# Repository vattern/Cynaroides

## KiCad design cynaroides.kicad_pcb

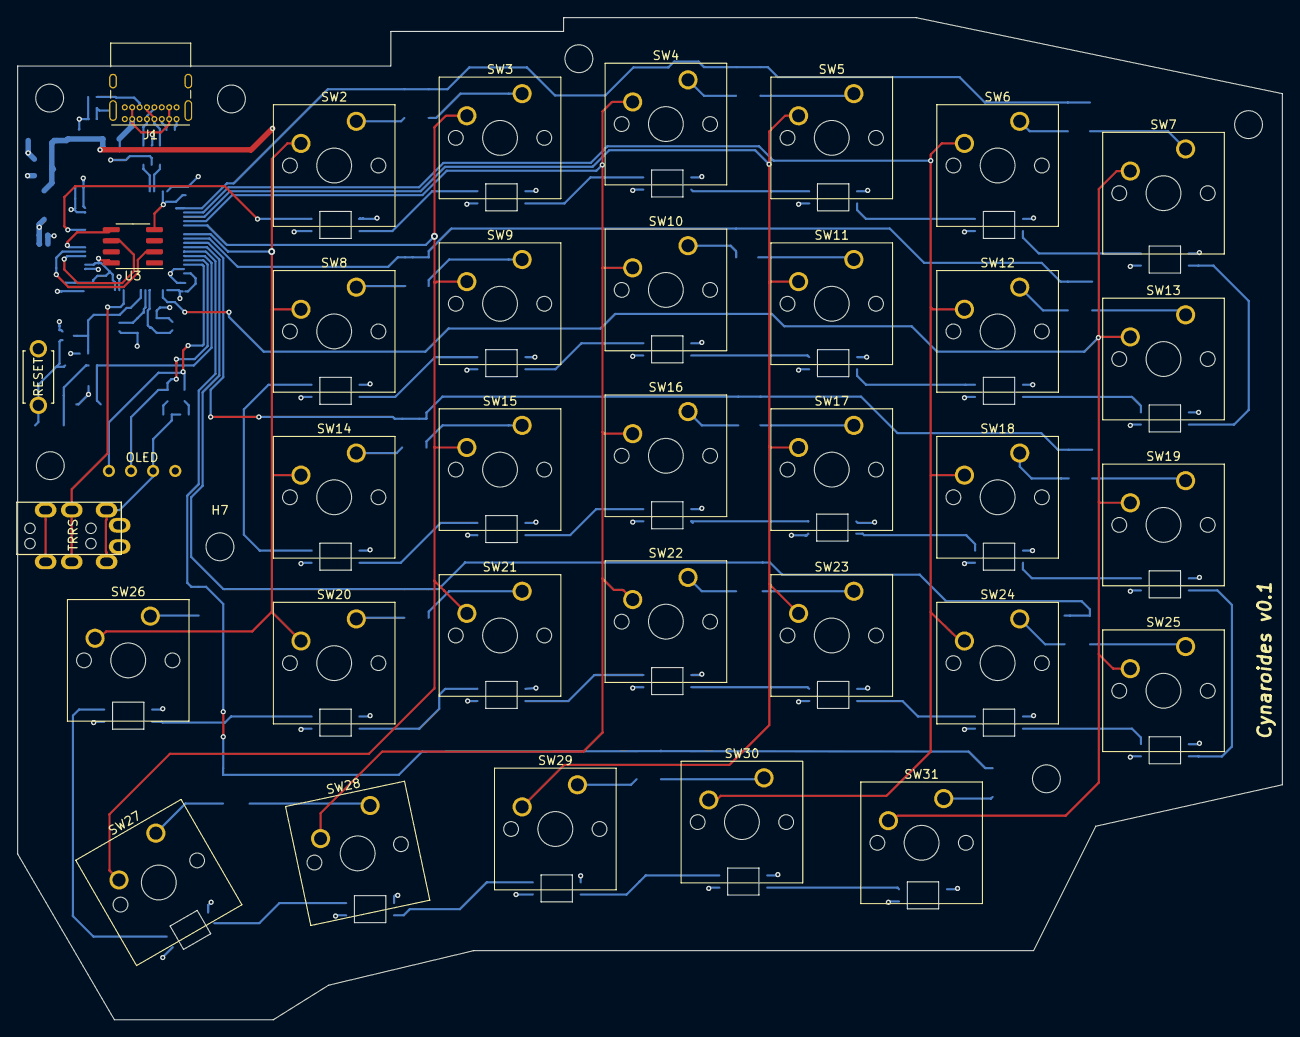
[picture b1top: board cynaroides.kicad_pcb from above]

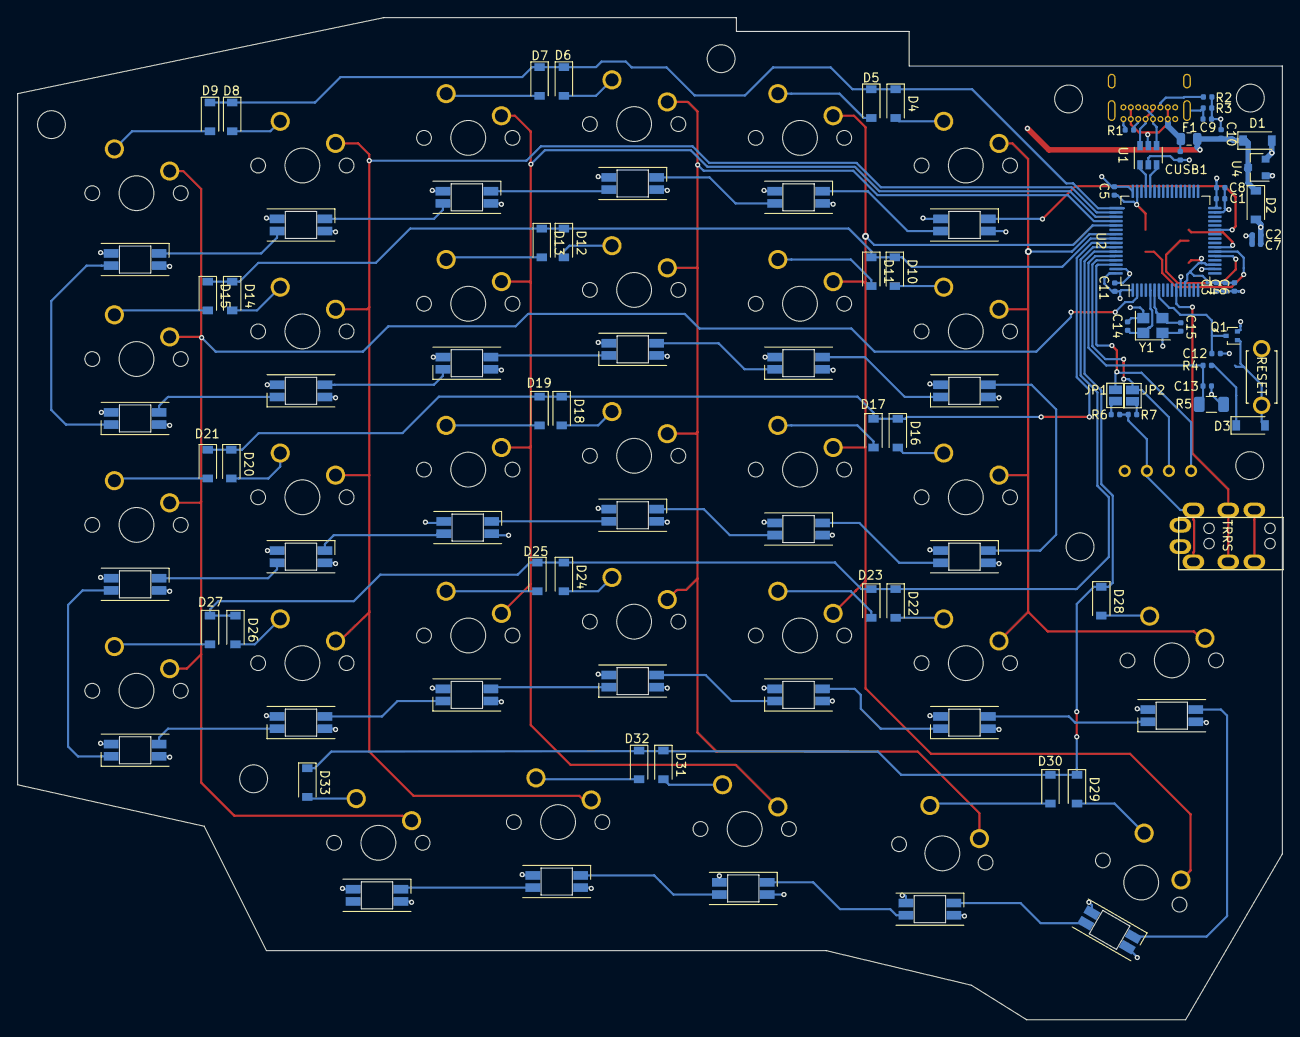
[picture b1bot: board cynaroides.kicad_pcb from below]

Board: 4 copper layers, 145.2 x 115.0 mm, 136 parts (94 on the bottom side), 96 nets.

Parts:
C1, C2, C5, C6, C10, C11, C12: 100n; C_0402_1005Metric
C3: 10n; C_0402_1005Metric
C4: 1u; C_0402_1005Metric
C7, C8: 4u7; C_0402_1005Metric
C9: 4n7; C_0402_1005Metric
C13: 100u; C_0402_1005Metric
C14, C15: 22p; C_0402_1005Metric
CUSB1: 100n; C_0402_1005Metric
D1: D_Schottky; D_SOD-123
D2: D_TVS; D_SOD-123
D3, D4, D5, D6, D7, D8, D9, D10, D11, D12, D13, D14, D15, D16, D17, D18, D19, D20, D21, D22, D23, D24, D25, D26, D27, D28, D29, D30, D31, D32, D33: 1N4148W; D_SOD-123
D34, D35, D36, D37, D38, D39, D40, D41, D42, D43, D44, D45, D46, D47, D48, D49, D50, D51, D52, D53, D54, D55, D56, D57, D58, D59, D60, D61, D62, D63: SK6812MINI; YS-SK6812MINI-E
F1: Polyfuse_Small; Fuse_0805_2012Metric
H1, H2, H3, H4, H5, H6, H7: MountingHole; MountingHole_3.2mm_M3
J1: USB_C_Receptacle_USB2.0; USB_C_Receptacle_GCT_USB4085
J2: MJ-4PP-9
JP1, JP2: Jumper_NC_Small; SolderJumper-2_P1.3mm_Open_Pad1.0x1.5mm
OL1: OLED; OLED_v2
Q1: DTC123J; SOT-416
R1, R2: 5k1; R_0402_1005Metric
R3: 1M; R_0402_1005Metric
R4: 33k; R_0402_1005Metric
R5: 100k; R_1206_3216Metric
R6, R7: 4k7; R_0402_1005Metric
SW1: SW_Push; ResetSW
SW2, SW3, SW4, SW5, SW6, SW7, SW8, SW9, SW10, SW11, SW12, SW13, SW14, SW15, SW16, SW17, SW18, SW19, SW20, SW21, SW22, SW23, SW24, SW25, SW26, SW27, SW28, SW29, SW30, SW31: SW_Push; SW_Cherry_MX_1.00u_PCB
U1: USBLC6-2SC6; SOT-23-6
U2: STM32F411RCTx; LQFP-64_10x10mm_P0.5mm
U3: 25LCxxx; SOIC-8_3.9x4.9mm_P1.27mm
U4: MCP1700-3302E_SOT23; SOT-23
Y1: Crystal_GND24_Small; Crystal_SMD_3225-4Pin_3.2x2.5mm

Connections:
+3V3: C1.2, C2.2, C3.2, C4.2, C5.2, C6.2, C7.2, C8.2, C11.2, D1.2, J2.D, OL1.3, R6.2, R7.2, SW1.1, U2.1, U2.13, U2.19, U2.32, U2.48, U2.64, U3.8, U4.2
+5V: C10.2, D1.1, D2.1, D34.4, D35.4, D36.4, D37.4, D38.4, D39.4, D40.4, D41.4, D42.4, D43.4, D44.4, D45.4, D46.4, D47.4, D48.4, D49.4, D50.4, D51.4, D52.4, D53.4, D54.4, D55.4, D56.4, D57.4, D58.4, D59.4, D60.4, D61.4, D62.4, D63.4, F1.1, U4.3
BOOT0: C13.2, R4.1, R5.2, U2.60
COL0: SW2.2, SW8.2, SW14.2, SW20.2, SW26.2, U2.55
COL1: SW3.2, SW9.2, SW15.2, SW21.2, SW27.2, U2.53
COL2: SW4.2, SW10.2, SW16.2, SW22.2, SW28.2, U2.52
COL3: SW5.2, SW11.2, SW17.2, SW23.2, SW29.2, U2.51
COL4: SW6.2, SW12.2, SW18.2, SW24.2, SW30.2, U2.50
COL5: SW7.2, SW13.2, SW19.2, SW25.2, SW31.2, U2.2
D+: U1.1, U2.45
D-: U1.3, U2.44
DBus+: J1.A6, J1.B6, U1.6
DBus-: J1.A7, J1.B7, U1.4
GND: C1.1, C2.1, C3.1, C4.1, C5.1, C6.1, C7.1, C8.1, C9.2, C10.1, C11.1, C12.1, C13.1, C14.2, C15.2, CUSB1.1, D2.2, D34.2, D35.2, D36.2, D37.2, D38.2, D39.2, D40.2, D41.2, D42.2, D43.2, D44.2, D45.2, D46.2, D47.2, D48.2, D49.2, D50.2, D51.2, D52.2, D53.2, D54.2, D55.2, D56.2, D57.2, D58.2, D59.2, D60.2, D61.2, D62.2, D63.2, J1.A1, J1.A12, J1.B1, J1.B12, J2.A, OL1.4, Q1.2, R1.1, R2.1, R3.1, R5.1, U1.2, U2.12, U2.18, U2.31, U2.47, U2.63, U3.4, U4.1, Y1.2, Y1.4
LED: D34.3, U2.27
MISO: U2.22, U3.2
MOSI: U2.23, U3.5
NRST: C12.2, Q1.3, U2.7
unnamed: C9.1, J1.S1, R3.2
unnamed: C14.1, U2.5, Y1.1
unnamed: C15.1, U2.6, Y1.3
unnamed: D3.1, R4.2
unnamed: D3.2, Q1.1, SW1.2
unnamed: D4.2, SW2.1
unnamed: D5.2, SW3.1
unnamed: D6.2, SW4.1
unnamed: D7.2, SW5.1
unnamed: D8.2, SW6.1
unnamed: D9.2, SW7.1
unnamed: D10.2, SW8.1
unnamed: D11.2, SW9.1
unnamed: D12.2, SW10.1
unnamed: D13.2, SW11.1
unnamed: D14.2, SW12.1
unnamed: D15.2, SW13.1
unnamed: D16.2, SW14.1
unnamed: D17.2, SW15.1
unnamed: D18.2, SW16.1
unnamed: D19.2, SW17.1
unnamed: D20.2, SW18.1
unnamed: D21.2, SW19.1
unnamed: D22.2, SW20.1
unnamed: D23.2, SW21.1
unnamed: D24.2, SW22.1
unnamed: D25.2, SW23.1
unnamed: D26.2, SW24.1
unnamed: D27.2, SW25.1
unnamed: D28.2, SW26.1
unnamed: D29.2, SW27.1
unnamed: D30.2, SW28.1
unnamed: D31.2, SW29.1
unnamed: D32.2, SW30.1
unnamed: D33.2, SW31.1
unnamed: D34.1, D35.3
unnamed: D35.1, D36.3
unnamed: D36.1, D37.3
unnamed: D37.1, D38.3
unnamed: D38.1, D39.3
unnamed: D39.1, D40.3
unnamed: D40.1, D41.3
unnamed: D41.1, D42.3
unnamed: D42.1, D43.3
unnamed: D43.1, D44.3
unnamed: D44.1, D45.3
unnamed: D45.1, D46.3
unnamed: D46.1, D47.3
unnamed: D47.1, D48.3
unnamed: D48.1, D49.3
unnamed: D49.1, D50.3
unnamed: D50.1, D51.3
unnamed: D51.1, D52.3
unnamed: D52.1, D53.3
unnamed: D53.1, D54.3
unnamed: D54.1, D55.3
unnamed: D55.1, D56.3
unnamed: D56.1, D57.3
unnamed: D57.1, D58.3
unnamed: D58.1, D59.3
unnamed: D59.1, D60.3
unnamed: D60.1, D61.3
unnamed: D61.1, D62.3
unnamed: D62.1, D63.3
unnamed: J1.A5, R1.2
unnamed: J1.B5, R2.2
unnamed: J2.C, U2.11
unnamed: JP1.1, R6.1
unnamed: JP2.1, R7.1
ROW0: D4.1, D5.1, D6.1, D7.1, D8.1, D9.1, U2.49
ROW1: D10.1, D11.1, D12.1, D13.1, D14.1, D15.1, U2.56
ROW2: D16.1, D17.1, D18.1, D19.1, D20.1, D21.1, U2.57
ROW3: D22.1, D23.1, D24.1, D25.1, D26.1, D27.1, U2.58
ROW4: D28.1, D29.1, D30.1, D31.1, D32.1, D33.1, U2.59
SCK: U2.21, U3.6
SCL: JP2.2, OL1.2, U2.61
SDA: JP1.2, OL1.1, U2.62
vbus: CUSB1.2, F1.2, J1.A4, J1.A9, J1.B4, J1.B9, U1.5

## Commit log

2021-01-16 Adding pcb files
